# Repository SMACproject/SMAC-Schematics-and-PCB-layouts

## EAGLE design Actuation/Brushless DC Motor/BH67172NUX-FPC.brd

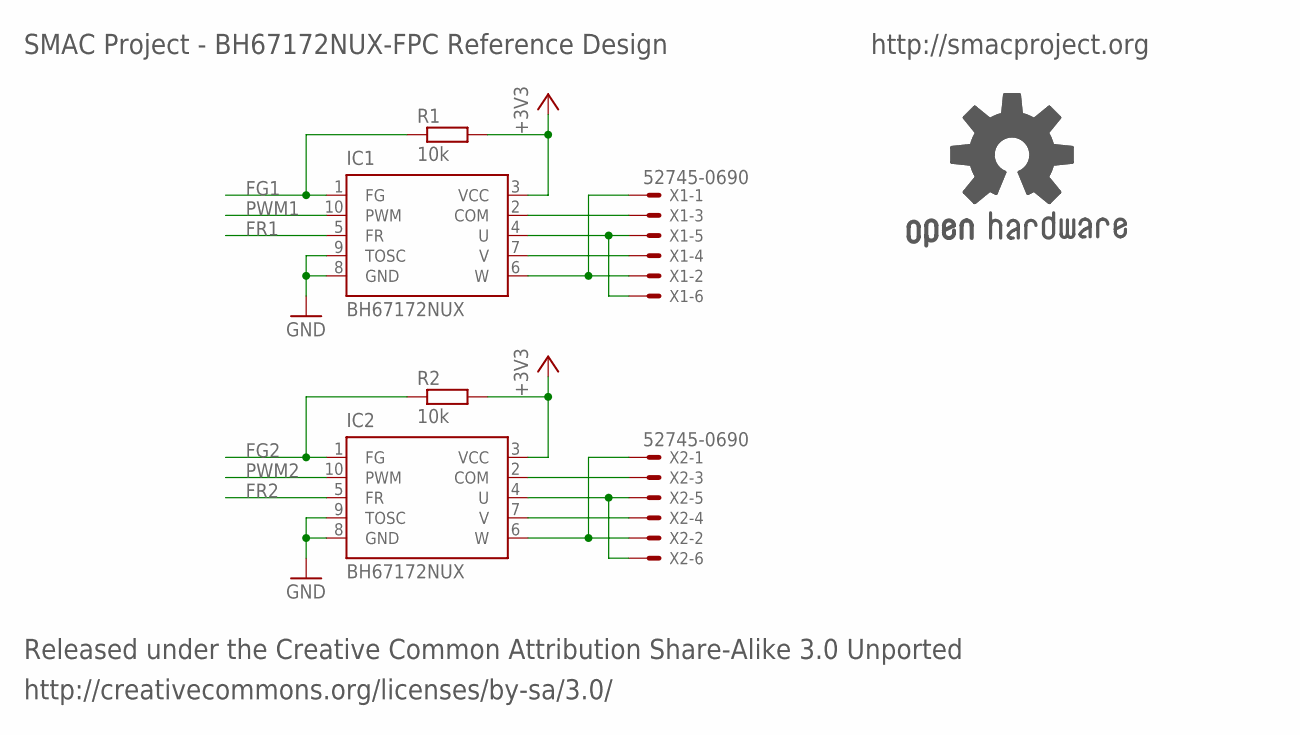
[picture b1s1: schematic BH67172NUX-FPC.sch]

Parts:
GOLD_ORB_SM1: OSHWLOGO_REF_SM; OSHW2REF
IC1, IC2: BH67172NUX; VSON010X3030
R1, R2: 10k; R0402
X1, X2: 52745-0690

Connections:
+3V3: IC1.3 (VCC), IC2.3 (VCC), R1.2, R2.2
COM1: IC1.2 (COM), X1.3
COM2: IC2.2 (COM), X2.3
FG1: IC1.1 (FG), R1.1
FG2: IC2.1 (FG), R2.1
FR1: IC1.5 (FR)
FR2: IC2.5 (FR)
GND: IC1.8 (GND), IC1.9 (TOSC), IC2.8 (GND), IC2.9 (TOSC)
PWM1: IC1.10 (PWM)
PWM2: IC2.10 (PWM)
U1: IC1.4 (U), X1.5, X1.6
U2: IC2.4 (U), X2.5, X2.6
V1: IC1.7 (V), X1.4
V2: IC2.7 (V), X2.4
W1: IC1.6 (W), X1.1, X1.2
W2: IC2.6 (W), X2.1, X2.2

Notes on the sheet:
Released under the Creative Common Attribution Share-Alike 3.0 Unported
http://creativecommons.org/licenses/by-sa/3.0/
SMAC Project - BH67172NUX-FPC Reference Design
http://smacproject.org

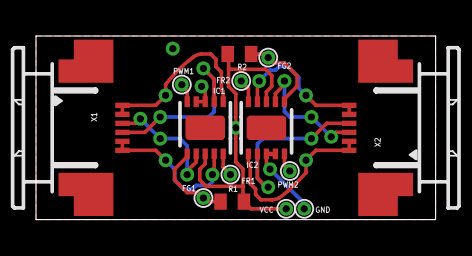
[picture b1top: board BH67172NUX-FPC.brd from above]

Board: 2 copper layers, 22.2 x 10.2 mm, 7 parts (0 on the bottom side), 12 nets.

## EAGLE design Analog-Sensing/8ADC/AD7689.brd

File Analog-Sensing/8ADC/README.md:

# 8ADC Module Reference Design

## Specification
- AD7689 16-bit analog to digital converter
- Solderable pads
- Board diameter 10mm

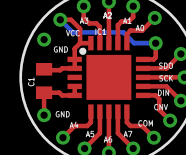
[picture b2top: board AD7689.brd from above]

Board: 2 copper layers, 3 parts (0 on the bottom side), 2 nets.

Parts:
C1: 10uF; C0402
GOLD_ORB_SM1: OSHWLOGO_REF_SM; OSHW2REF
IC1: AD7689; LFCSP20

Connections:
+3V3: C1.1, IC1.1, IC1.2, IC1.15, IC1.20
GND: C1.2, IC1.4, IC1.5

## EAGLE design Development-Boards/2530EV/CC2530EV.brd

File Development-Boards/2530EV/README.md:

# CC2530EV Reference Design

## Specification
- TI CC2530F256 with 256KB Flash and 8kB RAM
- Slim debugger connector, need an adapter to use with TI CC Debugger
- 2x 8-pins interface headers (P0 and P1)
- 1x power headers
- 1x reset button
- Board dimension 40mm x 40mm

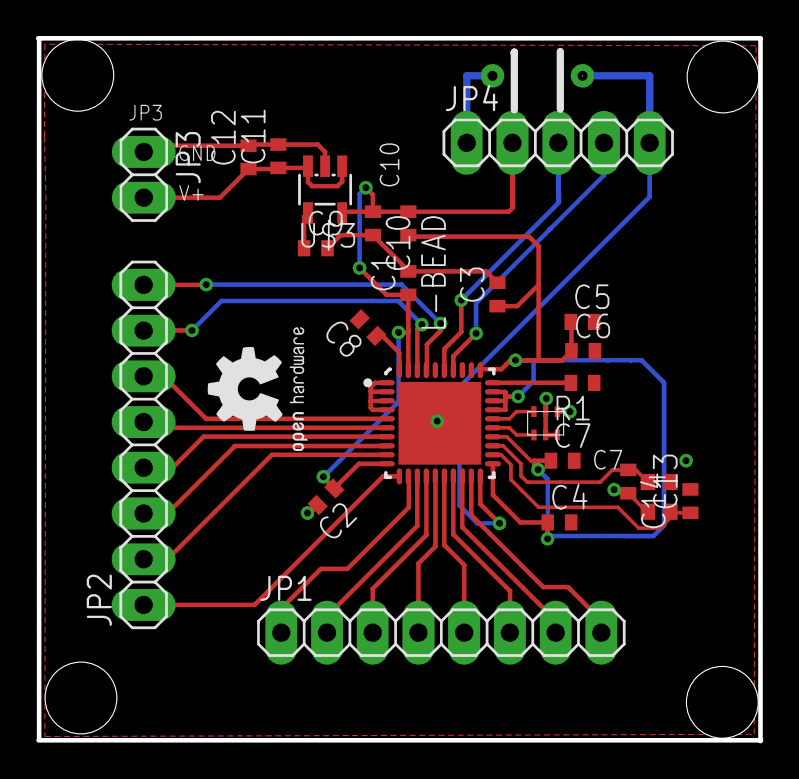
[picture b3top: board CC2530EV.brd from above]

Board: 2 copper layers, 40.2 x 39.0 mm, 26 parts (0 on the bottom side), 30 nets.

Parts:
C1, C2, C3, C4, C5, C6, C7, C9, C11: 100n; C0402
C8: 1u; C0402
C10, C12: 2u2; C0402
C13, C14: 27p; C0402
GOLD_ORB_SM1: OSHWLOGO_GOLD_ORB_SM; OSHW2
JP1, JP2: 1X08
JP3: 1X02
JP4: 1X05
L-BEAD: L-BEAD
R1: 56K; R0402
U$1: CC2530; QFN50P600X600X100-41N
U$2: 24530BM15A0002
U$3: TPS732XX; SOT23
U$4: XTAL32M; 2.5X2X0.5
U$5: PUSH_BOT; EVQ_11_TH

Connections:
DBG_DC: JP4.4, U$1.34
DBG_DD: JP4.3, U$1.35
GND: C1.2, C2.2, C3.2, C4.2, C5.2, C6.2, C7.2, C8.2, C9.2, C10.2, C11.2, C12.2, C13.2, C14.2, JP3.1, JP4.1, R1.1, U$1.1, U$1.2, U$1.3, U$1.4, U$1.41, U$2.P$2, U$2.P$5, U$2.P$6, U$3.2, U$4.P$2, U$4.P$4, U$5.P$2
unnamed: C8.1, U$1.40
unnamed: R1.2, U$1.30
unnamed: U$1.25, U$2.P$4
unnamed: U$1.26, U$2.P$3
unnamed: C9.1, U$3.4
unnamed: C14.1, U$1.23, U$4.P$1
unnamed: C13.1, U$1.22, U$4.P$3
unnamed: JP1.1, U$1.12
unnamed: JP1.2, U$1.13
unnamed: JP1.3, U$1.14
unnamed: JP1.4, U$1.15
unnamed: JP1.5, U$1.16
unnamed: JP1.6, U$1.17
unnamed: JP1.7, U$1.18
unnamed: JP1.8, U$1.19
unnamed: JP2.1, U$1.11
unnamed: JP2.2, U$1.9
unnamed: JP2.3, U$1.8
unnamed: JP2.4, U$1.7
unnamed: JP2.5, U$1.6
unnamed: JP2.6, U$1.5
unnamed: JP2.7, U$1.38
unnamed: JP2.8, U$1.37
RESET: JP4.5, U$1.20, U$5.P$1
V+: C11.1, C12.1, JP3.2, U$3.1, U$3.3
VCC: C3.1, C4.1, C5.1, C6.1, C7.1, L-BEAD.2, U$1.21, U$1.24, U$1.27, U$1.28, U$1.29, U$1.31
VDD: C1.1, C2.1, C10.1, JP4.2, L-BEAD.1, U$1.10, U$1.39, U$3.5

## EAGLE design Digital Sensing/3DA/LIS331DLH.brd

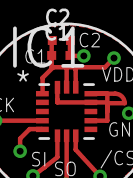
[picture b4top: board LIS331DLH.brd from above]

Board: 2 copper layers, 4 parts (0 on the bottom side), 2 nets.

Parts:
C1: 100n; C0402
C2: 10u; C0402
GOLD_ORB_SM2: OSHWLOGO_REF_SM; OSHW2REF
IC1: LIS331DLH; LGA16R50P3X5_300X300X100

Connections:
GND: C1.2, C2.2, IC1.5, IC1.10, IC1.12, IC1.13, IC1.16
VDD: C1.1, C2.1, IC1.1, IC1.14, IC1.15

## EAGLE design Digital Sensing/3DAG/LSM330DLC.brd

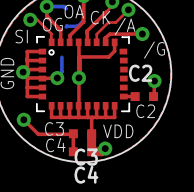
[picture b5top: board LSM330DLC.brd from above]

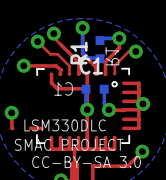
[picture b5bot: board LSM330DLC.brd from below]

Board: 2 copper layers, 7 parts (2 on the bottom side), 5 nets.

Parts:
C1, C3: 100n; C0402
C2: 4.7u; C0402
C4: 10u; C0402
GOLD_ORB_SM2: OSHWLOGO_REF_SM; OSHW2REF
IC1: LSM330DLC
R1: 0; R0402

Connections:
GND: C1.2, C2.2, C3.2, C4.2, IC1.GND1, IC1.GND2, IC1.RES1, IC1.RES2, IC1.RES3, IC1.RES4
unnamed: C2.1, IC1.CAP
SDOA: IC1.SDOA, R1.2
SDOG: IC1.SDOG, R1.1
VDD: C1.1, C3.1, C4.1, IC1.RES5, IC1.RES6, IC1.RES7, IC1.RES8, IC1.RES9, IC1.VDD1, IC1.VDD2, IC1.VDD3, IC1.VDDIO1, IC1.VDDIO2

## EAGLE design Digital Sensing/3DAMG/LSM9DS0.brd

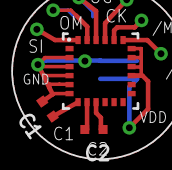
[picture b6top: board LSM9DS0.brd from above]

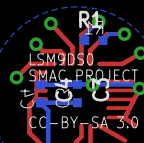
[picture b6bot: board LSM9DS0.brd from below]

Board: 2 copper layers, 7 parts (3 on the bottom side), 7 nets.

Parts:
C1: 4.7uF; C0402
C2: 0.22uF; C0402
C3: 10uF; C0402
C4: 100nF; C0402
GOLD_ORB_SM2: OSHWLOGO_REF_SM; OSHW2REF
R1: R0402
U$1: LSM9DS09DOFS0; LGA24(4X4X1)

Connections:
GND: C1.2, C3.1, C4.1, U$1.P$2, U$1.P$3, U$1.P$4, U$1.P$5, U$1.P$6
unnamed: C1.1, U$1.P$7
unnamed: C2.2, U$1.P$8
unnamed: C2.1, U$1.P$9
SDO_G: R1.1, U$1.P$22
SDO_XM: R1.2, U$1.P$23
VDD: C3.2, C4.2, U$1.P$15, U$1.P$16, U$1.P$17, U$1.P$18

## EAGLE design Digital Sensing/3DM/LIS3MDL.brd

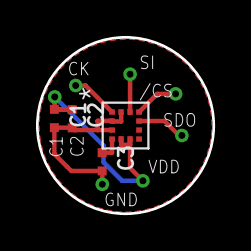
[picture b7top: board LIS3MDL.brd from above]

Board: 2 copper layers, 9.8 x 9.8 mm, 5 parts (0 on the bottom side), 3 nets.

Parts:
C1: 1u; C0402
C2, C3: 100n; C0402
GOLD_ORB_SM1: OSHWLOGO_REF_SM; OSHW2REF
U$3: LIS3MDL; VFLGA-2X2X1

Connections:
GND: C1.2, C2.2, C3.2, U$3.P$2, U$3.P$3, U$3.P$12
unnamed: C3.1, U$3.P$4
VDD: C1.1, C2.1, U$3.P$5, U$3.P$6

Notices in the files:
Actuation/Brushless DC Motor/BH67172NUX-FPC.brd:
CC-BY-SA 3.0
parts and their libraries:
rc-master-smd: Copyright (C) 2007, Bob Starr
SparkFun-Sensors: Licensing: Creative Commons ShareAlike 4.0 International - https://creativecommons.org/licenses/by-sa/4.0
